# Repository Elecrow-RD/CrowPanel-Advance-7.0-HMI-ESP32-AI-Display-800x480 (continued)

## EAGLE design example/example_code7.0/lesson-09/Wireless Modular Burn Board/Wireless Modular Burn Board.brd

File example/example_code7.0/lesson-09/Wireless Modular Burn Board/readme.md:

### Wirless Module H2/C6 Special board burning mode

##### 1.Gather the necessary tools

|      | tools                    | quantity |
| ---- | ------------------------ | -------- |
| 1    | Wirless Module H2/C6     | 1        |
| 2    | wirless Module_testboard | 1        |

Wirless Module H2/C6

wirless Module_testboard

##### 2.wiring

Wirless Module H2/C6 Insert in the direction of the arrow.

##### 3.Burning

Connect the serial module to the computer and find the corresponding serial device number (e.g. COM35) in the Task Manager.

Open Arduino or open the corresponding serial port under any serial port tool.

Press and hold the BOOT key and then press the RST key to enter burn mode.

The serial monitor prints to enter burn-in mode.

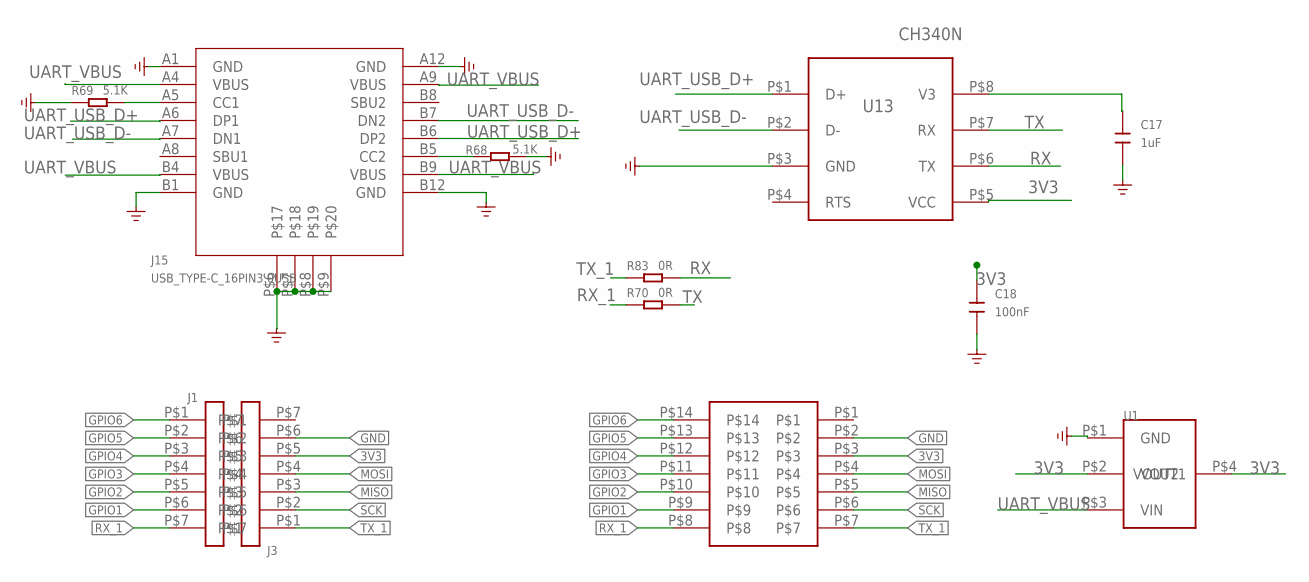
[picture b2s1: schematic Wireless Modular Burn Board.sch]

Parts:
C17: 1uF; 0603
C18: 100nF; 0603
J1, J3: 2.54MM-7P
J2: SMT-2.54MM-7P
J15: USB_TYPE-C_16PIN3.0USB; KEVIN_3.0TYPEC-SMD
R68, R69: 5.1K; DISCRETE_R0603
R70, R83: 0R; DISCRETE_R0603
U1: AMS1117-3V3; SOT-223
U13: CH340N; SOP8

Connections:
3V3: C18.2, J2.P$3, J3.P$5, U1.P$2 (VOUT1), U1.P$4 (VOUT2), U13.P$5 (VCC)
GND: C17.1, C18.1, J2.P$2, J3.P$6, J15.A1 (GND), J15.A12 (GND), J15.B1 (GND), J15.B12 (GND), J15.P$6, J15.P$7, J15.P$8, J15.P$9, R68.2, R69.1, U1.P$1 (GND), U13.P$3 (GND)
GPIO1: J1.P$6, J2.P$9
GPIO2: J1.P$5, J2.P$10
GPIO3: J1.P$4, J2.P$11
GPIO4: J1.P$3, J2.P$12
GPIO5: J1.P$2, J2.P$13
GPIO6: J1.P$1, J2.P$14
MISO: J2.P$5, J3.P$3
MOSI: J2.P$4, J3.P$4
unnamed: J15.B5 (CC2), R68.1
unnamed: J15.A5 (CC1), R69.2
unnamed: C17.2, U13.P$8 (V3)
RX: R83.2, U13.P$6 (TX)
RX_1: J1.P$7, J2.P$8, R70.1
SCK: J2.P$6, J3.P$2
TX: R70.2, U13.P$7 (RX)
TX_1: J2.P$7, J3.P$1, R83.1
UART_USB_D+: J15.A6 (DP1), J15.B6 (DP2), U13.P$1 (D+)
UART_USB_D-: J15.A7 (DN1), J15.B7 (DN2), U13.P$2 (D-)
UART_VBUS: J15.A4 (VBUS), J15.A9 (VBUS), J15.B4 (VBUS), J15.B9 (VBUS), U1.P$3 (VIN)

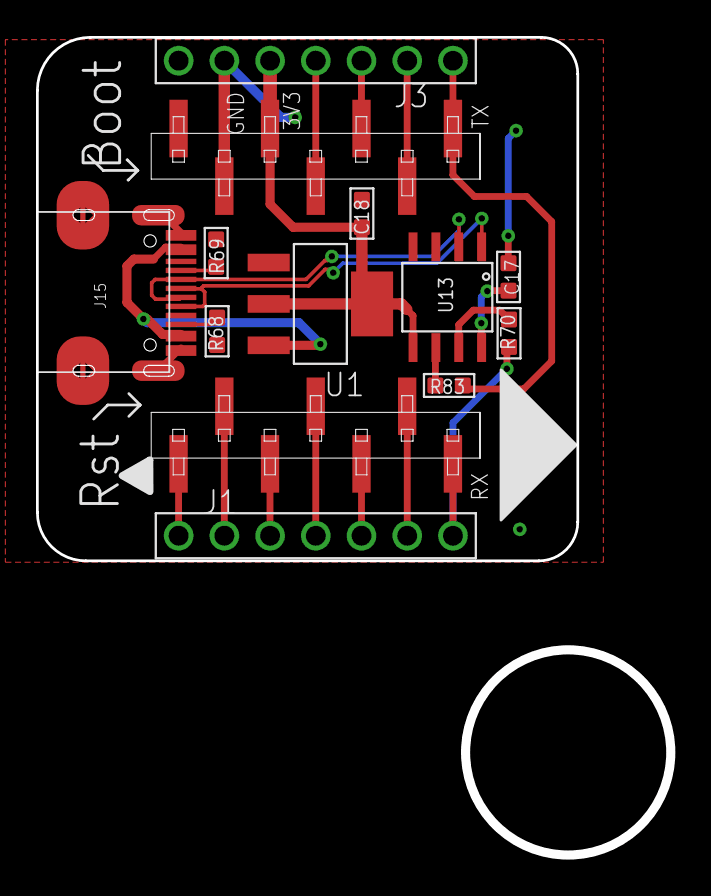
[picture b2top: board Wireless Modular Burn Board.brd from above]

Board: 2 copper layers, 30.0 x 29.1 mm, 12 parts (0 on the bottom side), 21 nets.

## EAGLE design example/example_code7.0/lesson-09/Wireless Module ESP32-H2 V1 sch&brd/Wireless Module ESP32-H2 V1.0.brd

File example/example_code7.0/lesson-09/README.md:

# **The ESP32-H2 module utilizes ZigBee technology to build a wireless Internet of Things** **example**

To complete this case, you need to refer to the detailed documentation tutorial, learn to burn code to utilizes ZigBee technology to build a wireless Internet and make the coordinator sends information to the terminal. Detailed documentation tutorials can be found at the bottom of the page.

***\*Note: All examples run on ESP32 version 3.0.2.\****

### **How to use example**

Learn how to set up the development board for serial communication with the wireless module. Learn how to use the official sample programs of ESP32-H2 to configure the wireless modules as a coordinator and a terminal node. After opening the sample code in the relevant code file with Arduino IDE.set the required configuration parameters and program it onto the development board.

***\*Configuration parameter：\****

For Coordinator configuration

For Terminal device configuration

For HMI Advance AI Display Configuration

### **How to add Arduino libraries**

Replace the libraries file with the following path:

C:\Users\user name\Documents\Arduio\libraries

***\*Note\****: The 'user name' here is the same as the user computer account name.

## **Documentation tutorial link****：**

## https://www.elecrow.com/wiki/9.ZigBee.html

## **Video** **tutorial link****：**
https://www.youtube.com/watch?v=UfxxT23T_bk

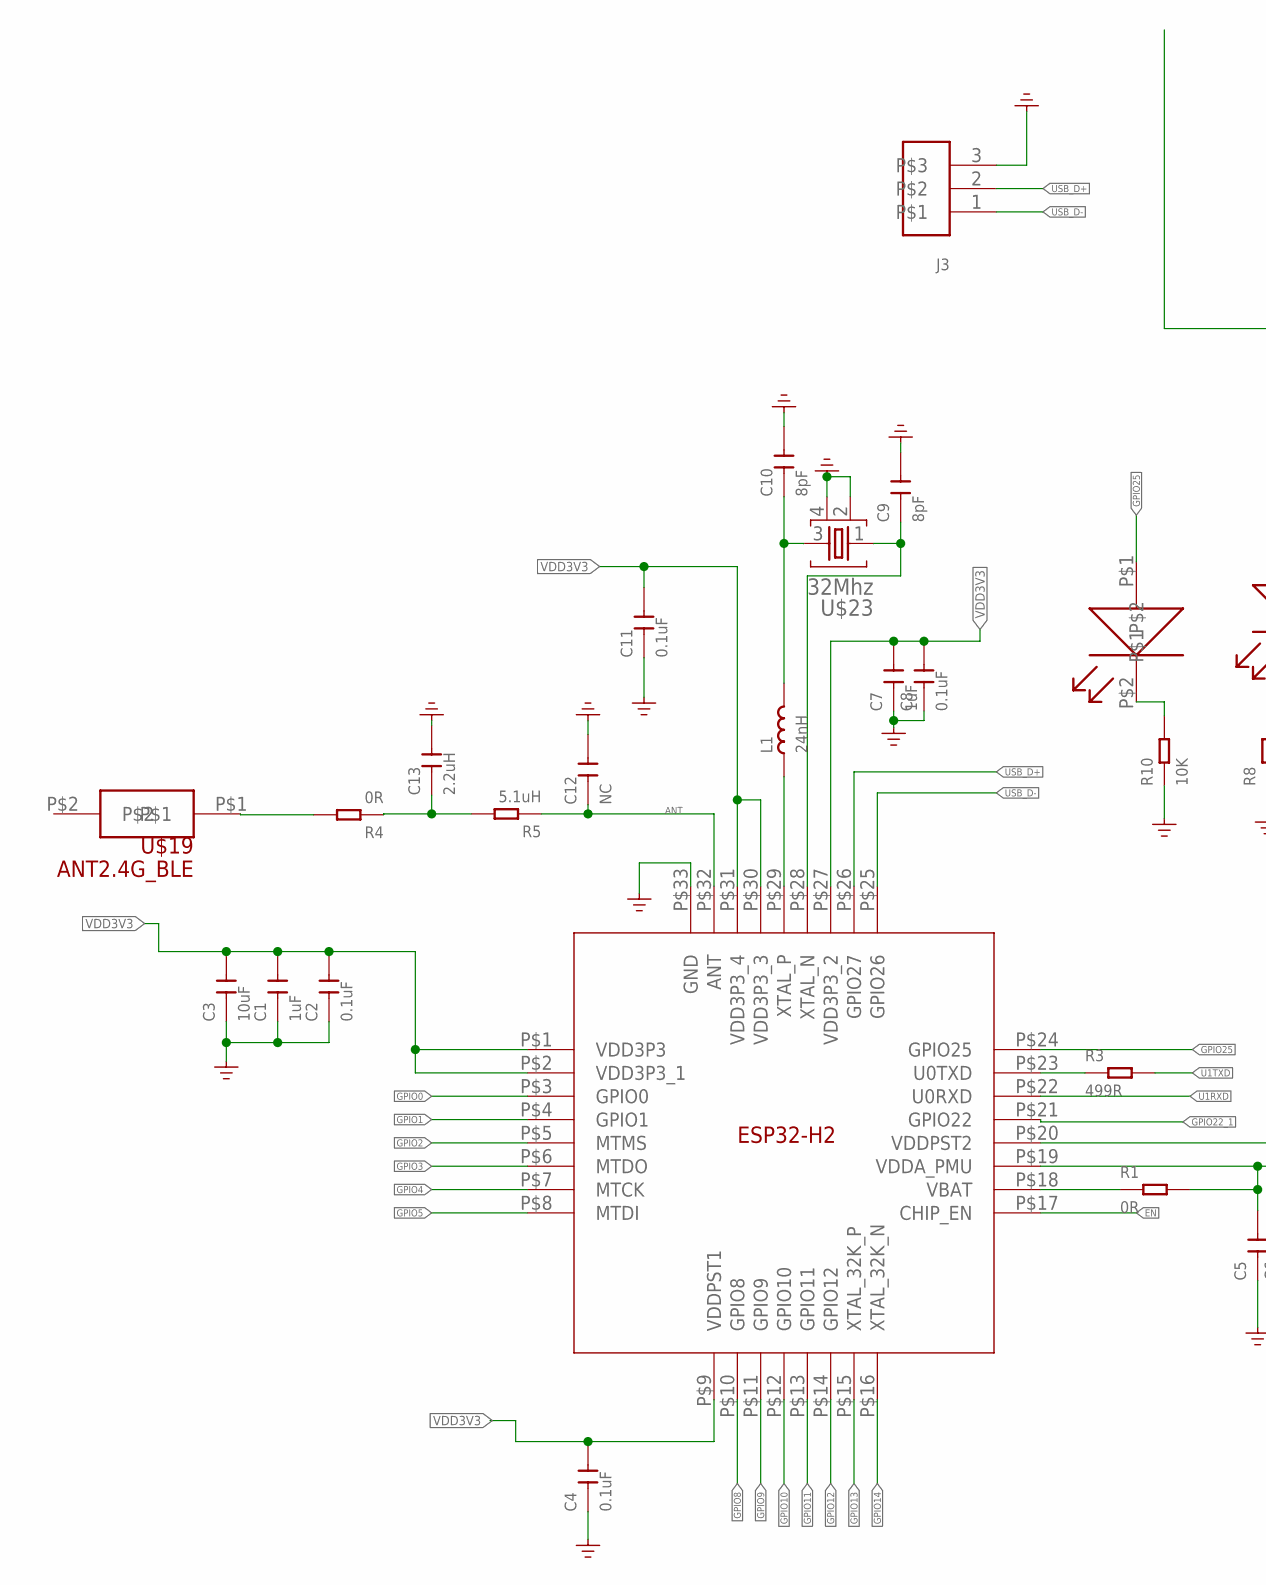
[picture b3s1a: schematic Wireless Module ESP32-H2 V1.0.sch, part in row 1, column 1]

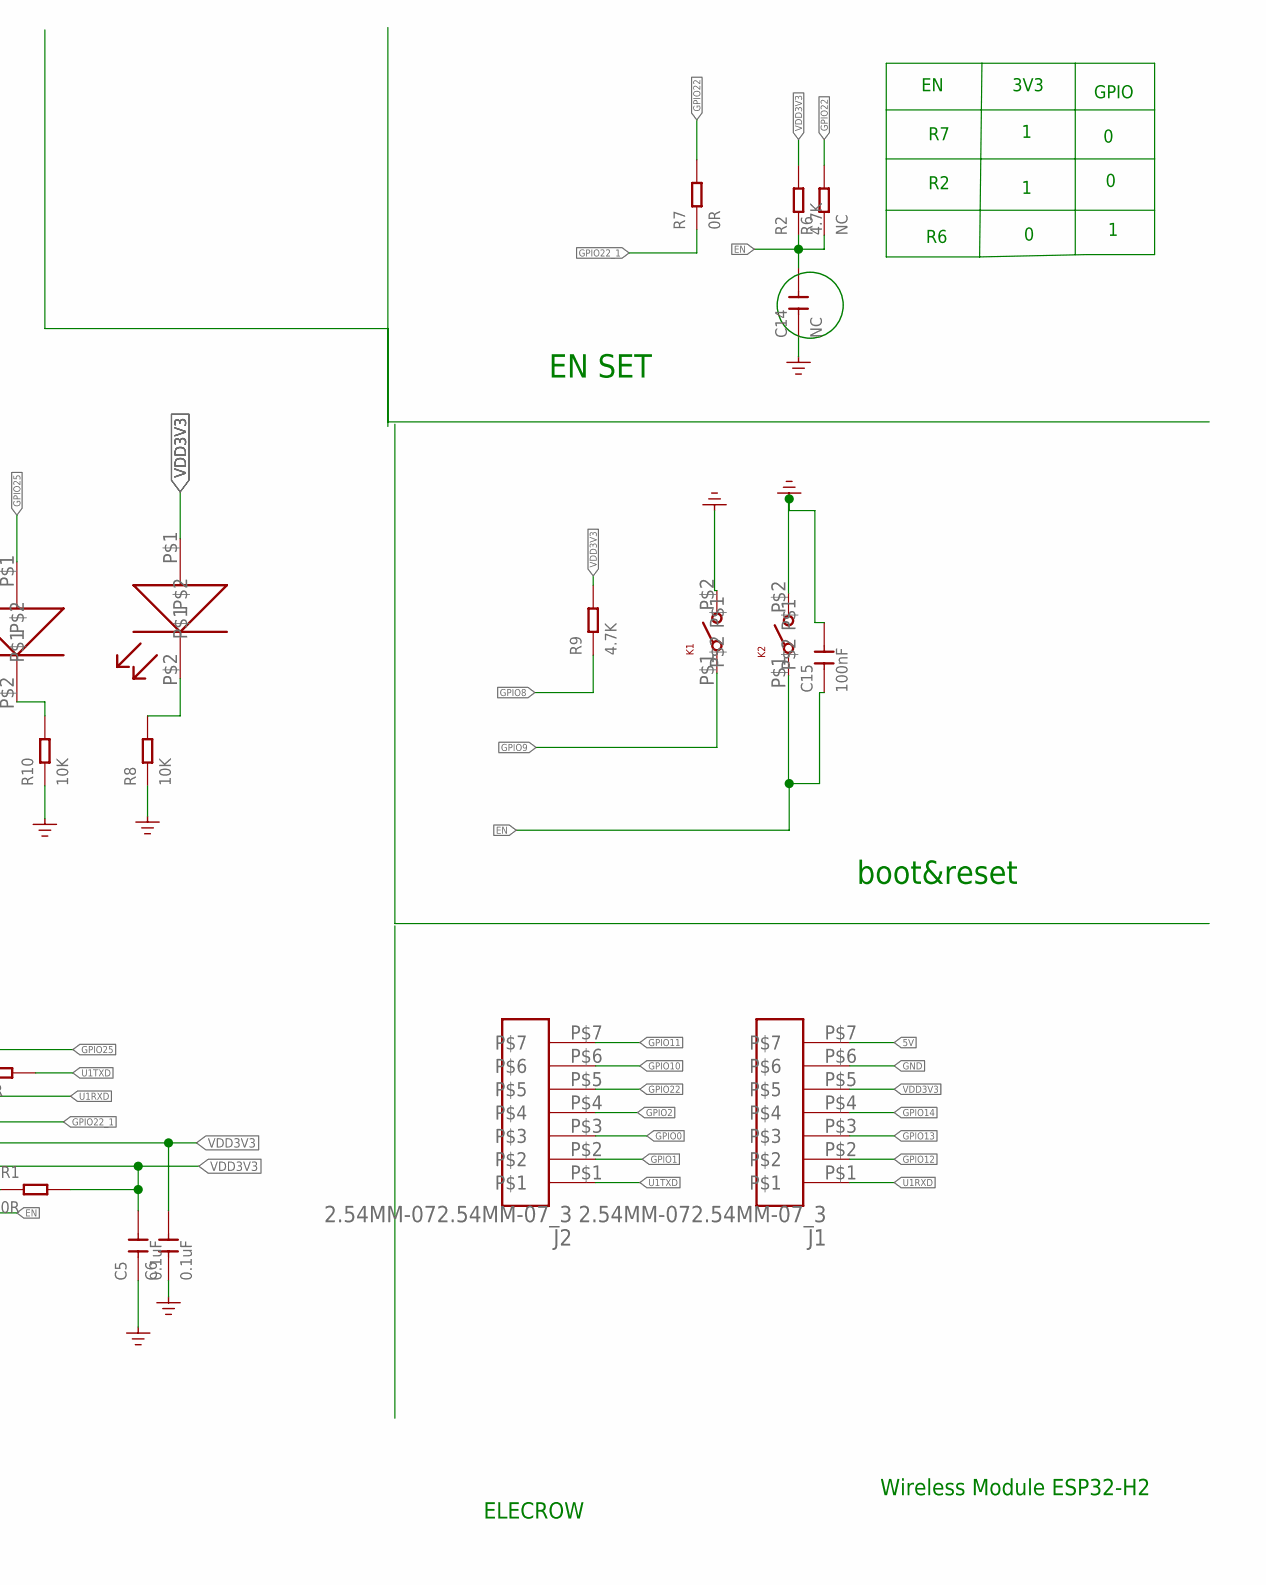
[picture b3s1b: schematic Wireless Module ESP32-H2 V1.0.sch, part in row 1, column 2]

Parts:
C1, C7: 1uF; DISCRETE-NEW_C0402
C2, C4, C5, C6, C8, C11: 0.1uF; DISCRETE-NEW_C0402
C3: 10uF; DISCRETE-NEW_C0402
C9, C10: 8pF; DISCRETE-NEW_C0402
C12, C14: NC; DISCRETE-NEW_C0402
C13: 2.2uH; DISCRETE-NEW_C0402
C15: 100nF; DISCRETE-NEW_C0402
J1, J2: 2.54MM-072.54MM-07_3; 2.54MM-07_3
J3: 1.27MM-3P
K1, K2: KEY_SMD; KEY_3*2.5
L1: 24nH; DISCRETE-NEW_L0402
LED1, LED2: LED_SMT; LED_0402
R1, R4, R7: 0R; DISCRETE-NEW_R0402
R2, R9: 4.7K; DISCRETE-NEW_R0402
R3: 499R; DISCRETE-NEW_R0402
R5: 5.1uH; DISCRETE-NEW_R0402
R6: NC; DISCRETE-NEW_R0402
R8, R10: 10K; DISCRETE-NEW_R0402
U$1: ESP32-H2
U$19: ANT2.4G_BLE; 2.4G_BLE
U$23: 32Mhz; NORDIC_NRF_BT-XTAL_2016_N

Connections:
5V: J1.P$7
ANT: C12.1, R5.1, U$1.P$32 (ANT)
EN: C14.2, C15.1, K2.P$1, R2.1, R6.1, U$1.P$17 (CHIP_EN)
GND: C1.1, C2.1, C3.1, C4.1, C5.1, C6.1, C7.1, C8.1, C9.2, C10.2, C11.1, C12.2, C13.2, C14.1, C15.2, J1.P$6, J3.3, K1.P$2, K2.P$2, R8.1, R10.1, U$1.P$33 (GND), U$23.2, U$23.4
GPIO0: J2.P$3, U$1.P$3 (GPIO0)
GPIO1: J2.P$2, U$1.P$4 (GPIO1)
GPIO2: J2.P$4, U$1.P$5 (MTMS)
GPIO3: U$1.P$6 (MTDO)
GPIO4: U$1.P$7 (MTCK)
GPIO5: U$1.P$8 (MTDI)
GPIO8: R9.1, U$1.P$10 (GPIO8)
GPIO9: K1.P$1, U$1.P$11 (GPIO9)
GPIO10: J2.P$6, U$1.P$12 (GPIO10)
GPIO11: J2.P$7, U$1.P$13 (GPIO11)
GPIO12: J1.P$2, U$1.P$14 (GPIO12)
GPIO13: J1.P$3, U$1.P$15 (XTAL_32K_P)
GPIO14: J1.P$4, U$1.P$16 (XTAL_32K_N)
GPIO22: J2.P$5, R6.2, R7.2
GPIO22_1: R7.1, U$1.P$21 (GPIO22)
GPIO25: LED1.P$1, U$1.P$24 (GPIO25)
unnamed: C13.1, R4.1, R5.2
unnamed: R3.1, U$1.P$23 (U0TXD)
unnamed: C10.1, L1.2, U$23.3
unnamed: C9.1, U$1.P$28 (XTAL_N), U$23.1
unnamed: LED2.P$2, R8.2
unnamed: LED1.P$2, R10.2
unnamed: R4.2, U$19.P$1
unnamed: L1.1, U$1.P$29 (XTAL_P)
P$18: R1.1, U$1.P$18 (VBAT)
U1RXD: J1.P$1, U$1.P$22 (U0RXD)
U1TXD: J2.P$1, R3.2
USB_D+: J3.2, U$1.P$26 (GPIO27)
USB_D-: J3.1, U$1.P$25 (GPIO26)
VDD3V3: C1.2, C2.2, C3.2, C4.2, C5.2, C6.2, C7.2, C8.2, C11.2, J1.P$5, LED2.P$1, R1.2, R2.2, R9.2, U$1.P$1 (VDD3P3), U$1.P$2 (VDD3P3_1), U$1.P$9 (VDDPST1), U$1.P$19 (VDDA_PMU), U$1.P$20 (VDDPST2), U$1.P$27 (VDD3P3_2), U$1.P$30 (VDD3P3_3), U$1.P$31 (VDD3P3_4)

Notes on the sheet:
3V3
GPIO
EN SET
boot&reset
ELECROW
Wireless Module ESP32-H2

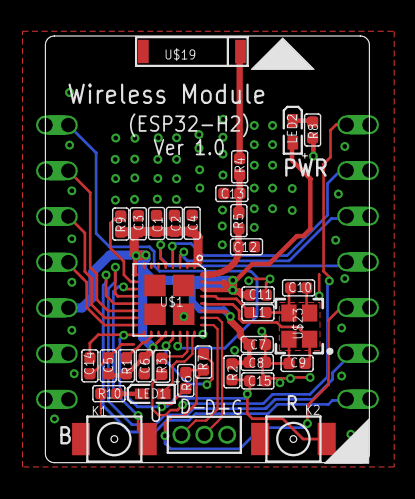
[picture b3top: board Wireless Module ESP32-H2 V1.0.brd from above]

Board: 2 copper layers, 18.0 x 23.7 mm, 36 parts (0 on the bottom side), 30 nets.

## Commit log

2025-03-15 Create readmemd
